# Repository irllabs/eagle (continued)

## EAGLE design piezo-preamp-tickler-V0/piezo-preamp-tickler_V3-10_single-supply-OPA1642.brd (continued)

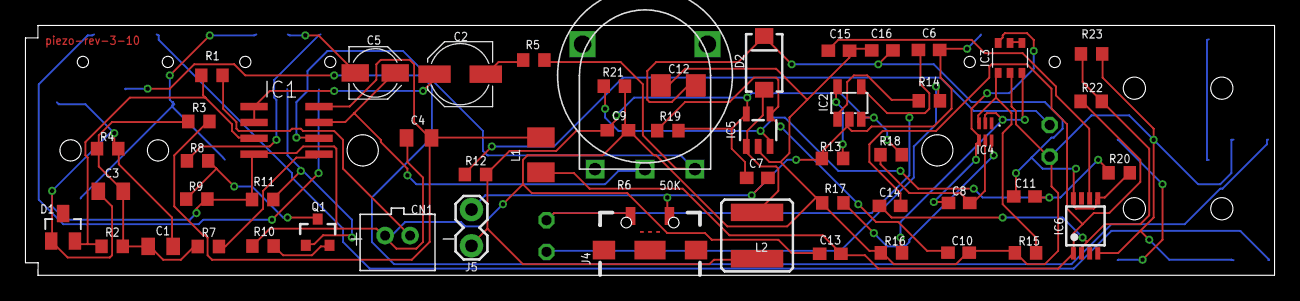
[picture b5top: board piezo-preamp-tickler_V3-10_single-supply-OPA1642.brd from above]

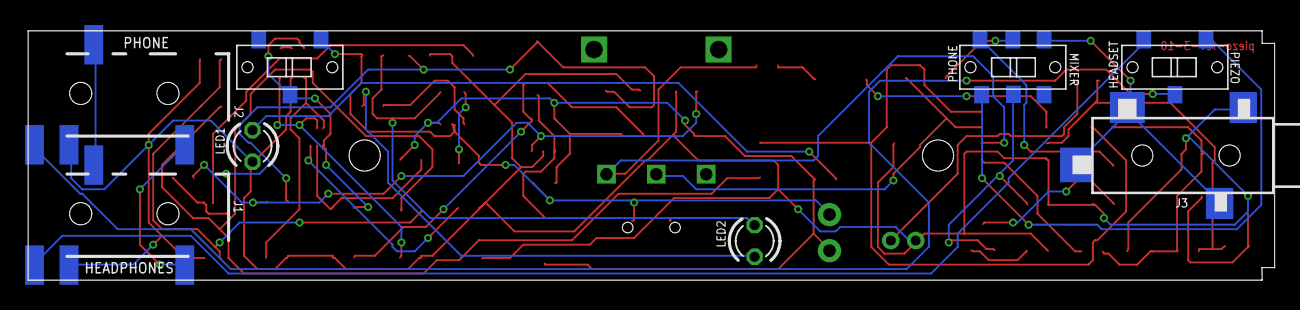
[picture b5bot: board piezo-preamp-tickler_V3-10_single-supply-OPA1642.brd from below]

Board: 2 copper layers, 100.0 x 20.0 mm, 61 parts (8 on the bottom side), 41 nets.

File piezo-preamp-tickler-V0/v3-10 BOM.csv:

"Part";"Value";"Device";"Package";"Description";"PROD_ID";"SPICEPREFIX";
"C1";"10uF";"C-USC0805K";"C0805K";"CAPACITOR, American symbol";"";"";
"C2";"100uF";"CPOL-EUC";"PANASONIC_C";"POLARIZED CAPACITOR, European symbol";"";"";
"C3";"0.1uF";"C-USC0805K";"C0805K";"CAPACITOR, American symbol";"";"";
"C4";"0.1uF";"C-USC0805K";"C0805K";"CAPACITOR, American symbol";"";"";
"C5";"10uF";"CPOL-EUB";"PANASONIC_B";"POLARIZED CAPACITOR, European symbol";"";"";
"C6";"4.7uF";"C-EUC0603";"C0603";"CAPACITOR, European symbol";"";"C";
"C7";"4.7uF";"C-EUC0603";"C0603";"CAPACITOR, European symbol";"";"C";
"C8";"0.1uF";"C-EUC0603";"C0603";"CAPACITOR, European symbol";"";"C";
"C9";"10uF";"C-EUC0603";"C0603";"CAPACITOR, European symbol";"";"C";
"C10";"56nF";"C-EUC0603";"C0603";"CAPACITOR, European symbol";"";"C";
"C11";"2.2pF";"C-EUC0603";"C0603";"CAPACITOR, European symbol";"";"C";
"C12";"68uF";"C-EUC1206";"C1206";"CAPACITOR, European symbol";"";"C";
"C13";"10uF";"C-EUC0603";"C0603";"CAPACITOR, European symbol";"";"C";
"C14";"10nF";"C-EUC0603";"C0603";"CAPACITOR, European symbol";"";"C";
"C15";"10nF";"C-EUC0603";"C0603";"CAPACITOR, European symbol";"";"C";
"C16";"10uF";"C-EUC0603";"C0603";"CAPACITOR, European symbol";"";"C";
"CN1";"";"JST_2PIN-THM";"JST-PH-2-THM";"JST 2-Pin Connectors of various flavors";"";"";
"D1";"BAT54S";"BAT54S";"SOT23";"Schottky Diodes";"";"";
"D2";"B130-13-F";"DIODESMA";"SMA-DIODE";"Diode";"";"";
"IC1";"OPA1642";"OPA1642";"SO08";"";"";"";
"IC2";"MCP73831";"MCP73831";"SOT-23-5";"";"";"";
"IC3";"QS6K1";"QS6K1";"SOT457R_PHILIPS";"";"";"";
"IC4";"BQ297X";"BQ297X-BATTERY-MANAGERLONG";"WSON-6-LONG";"";"";"";
"IC5";"SC4503";"SC4503";"SOT23-5";"";"";"";
"IC6";"TPS7A49";"TPS7A49";"MSOP-8";"";"";"";
"J1";"HEADPHONES";"TRRS-1/8"-3.5MMLGPADS";"TRRS_SJ-43514-SMT-TR";"Audio jack - 3.5mm TRRS variety - two rings.";"";"";
"J2";"PHONE";"TRRS-1/8"-3.5MMLGPADS";"TRRS_SJ-43514-SMT-TR";"Audio jack - 3.5mm TRRS variety - two rings.";"";"";
"J3";"Mixer";"TRS-1/8"-3.5MM";"TRS_SJ-3524-SMT";"";"";"";
"J4";"";"USB_MICRO-BREDUCED_PASTE";"USB-B-MICRO-SMD_RED_PASTE";"USB Type Micro-B Connector";"CONN-11752";"";
"J5";"Battery";"CONN_02LOCK";"1X02_LOCK";"Multi connection point. Often used as Generic Header-pin footprint for 0.1 inch spaced/style header connections";"";"";
"L1";"100uH/±5%/500mA";"L-EUL3225M";"L3225M";"INDUCTOR, European symbol";"";"L";
"L2";"2.7uH";"INDUCTORCR54";"CR54";"Inductors";"";"";
"LED1";"Power";"LED3MM";"LED3MM";"LED";"";"";
"LED2";"Charge";"LED3MM";"LED3MM";"LED";"";"";
"Q1";"MMBFJ201";"J201SOT-23";"SOT23-3";"N-channel JFET";"";"";
"R1";"100K";"R-US_R0603";"R0603";"RESISTOR, American symbol";"";"";
"R2";"10M";"R-US_R0603";"R0603";"RESISTOR, American symbol";"";"";
"R3";"100K";"R-US_R0603";"R0603";"RESISTOR, American symbol";"";"";
"R4";"100K";"R-US_R0603";"R0603";"RESISTOR, American symbol";"";"";
"R5";"2.2K";"R-US_R0603";"R0603";"RESISTOR, American symbol";"";"";
"R6";"50K";"POTTHUMBPOT14";"THUMBPOT14MM";"http://www.taydaelectronics.com/10k-ohm-linear-taper-potenti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";"";"";
"R7";"220";"R-US_R0603";"R0603";"RESISTOR, American symbol";"";"";
"R8";"1K";"R-US_R0603";"R0603";"RESISTOR, American symbol";"";"";
"R9";"1M";"R-US_R0603";"R0603";"RESISTOR, American symbol";"";"";
"R10";"1.2K";"R-US_R0603";"R0603";"RESISTOR, American symbol";"";"";
"R11";"2.2K";"R-US_R0603";"R0603";"RESISTOR, American symbol";"";"";
"R12";"390";"R-US_R0603";"R0603";"RESISTOR, American symbol";"";"";
"R13";"4.7K";"R-US_R0603";"R0603";"RESISTOR, American symbol";"";"";
"R14";"470";"R-US_R0603";"R0603";"RESISTOR, American symbol";"";"";
"R15";"10M";"R-US_R0603";"R0603";"RESISTOR, American symbol";"";"";
"R16";"10M";"R-US_R0603";"R0603";"RESISTOR, American symbol";"";"";
"R17";"2.2k";"R-US_R0603";"R0603";"RESISTOR, American symbol";"";"";
"R18";"330";"R-US_R0603";"R0603";"RESISTOR, American symbol";"";"";
"R19";"15k";"R-US_R0603";"R0603";"RESISTOR, American symbol";"";"";
"R20";"1M";"R-US_R0603";"R0603";"RESISTOR, American symbol";"";"";
"R21";"100k";"R-US_R0603";"R0603";"RESISTOR, American symbol";"";"";
"R22";"100k";"R-US_R0603";"R0603";"RESISTOR, American symbol";"";"";
"R23";"11k";"R-US_R0603";"R0603";"RESISTOR, American symbol";"";"";
"SW1";"SWITCH_DPDT";"SWITCH_DPDT";"SWITCH_DPDT_CL-SB-22B";"";"";"";
"SW2";"INPUT-select";"SWITCH_SPDTCL-SB-12B";"SWITCH_SPDT_CL-SB-12B";"";"";"";
"SW3";"SPDT";"SWITCH_SPDTCL-SB-12B";"SWITCH_SPDT_CL-SB-12B";"";"";"";

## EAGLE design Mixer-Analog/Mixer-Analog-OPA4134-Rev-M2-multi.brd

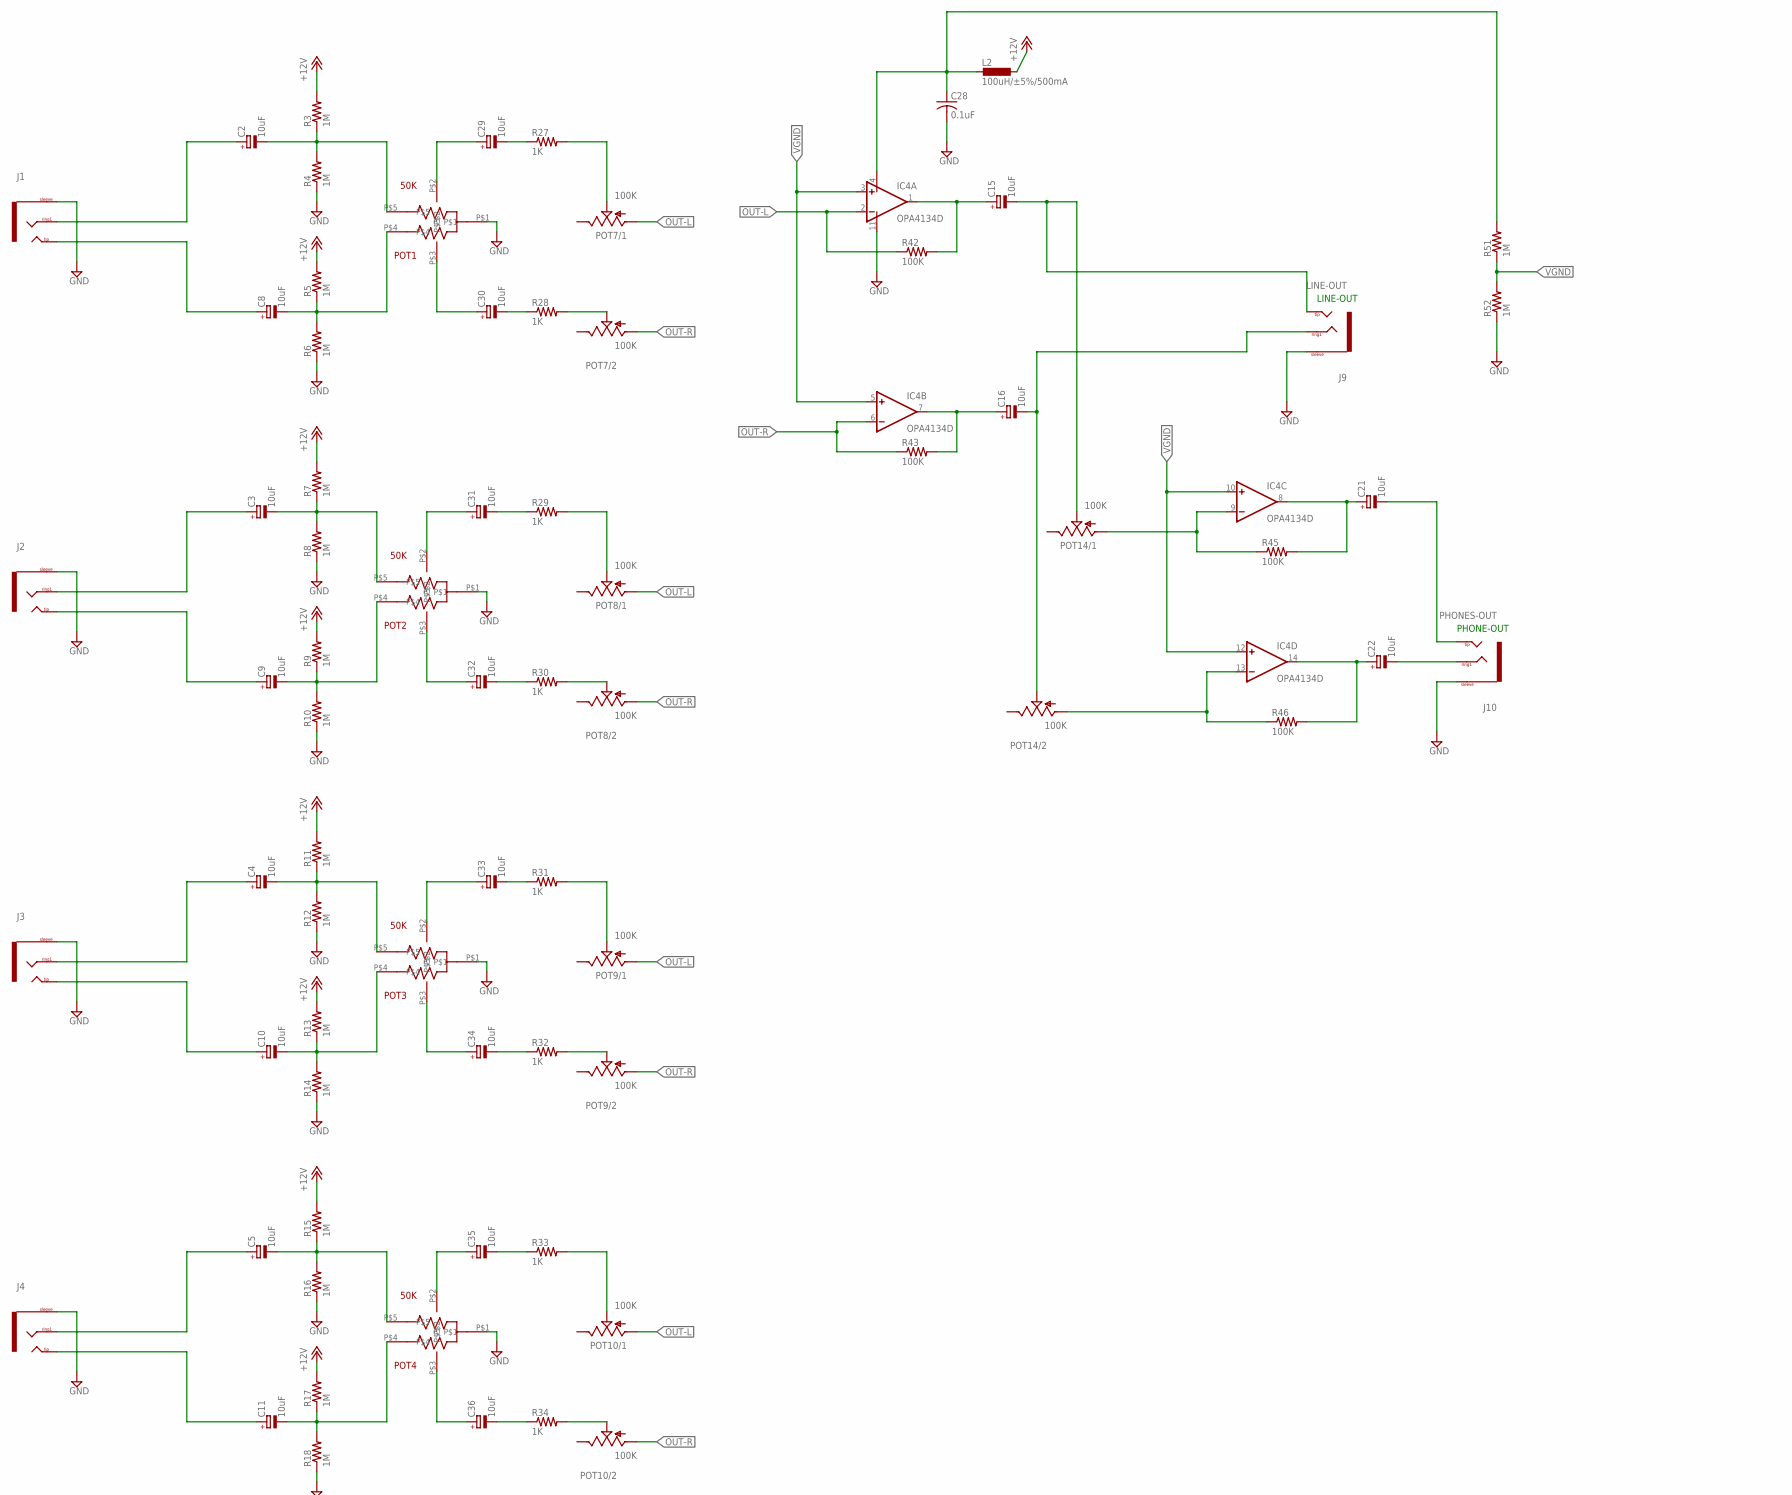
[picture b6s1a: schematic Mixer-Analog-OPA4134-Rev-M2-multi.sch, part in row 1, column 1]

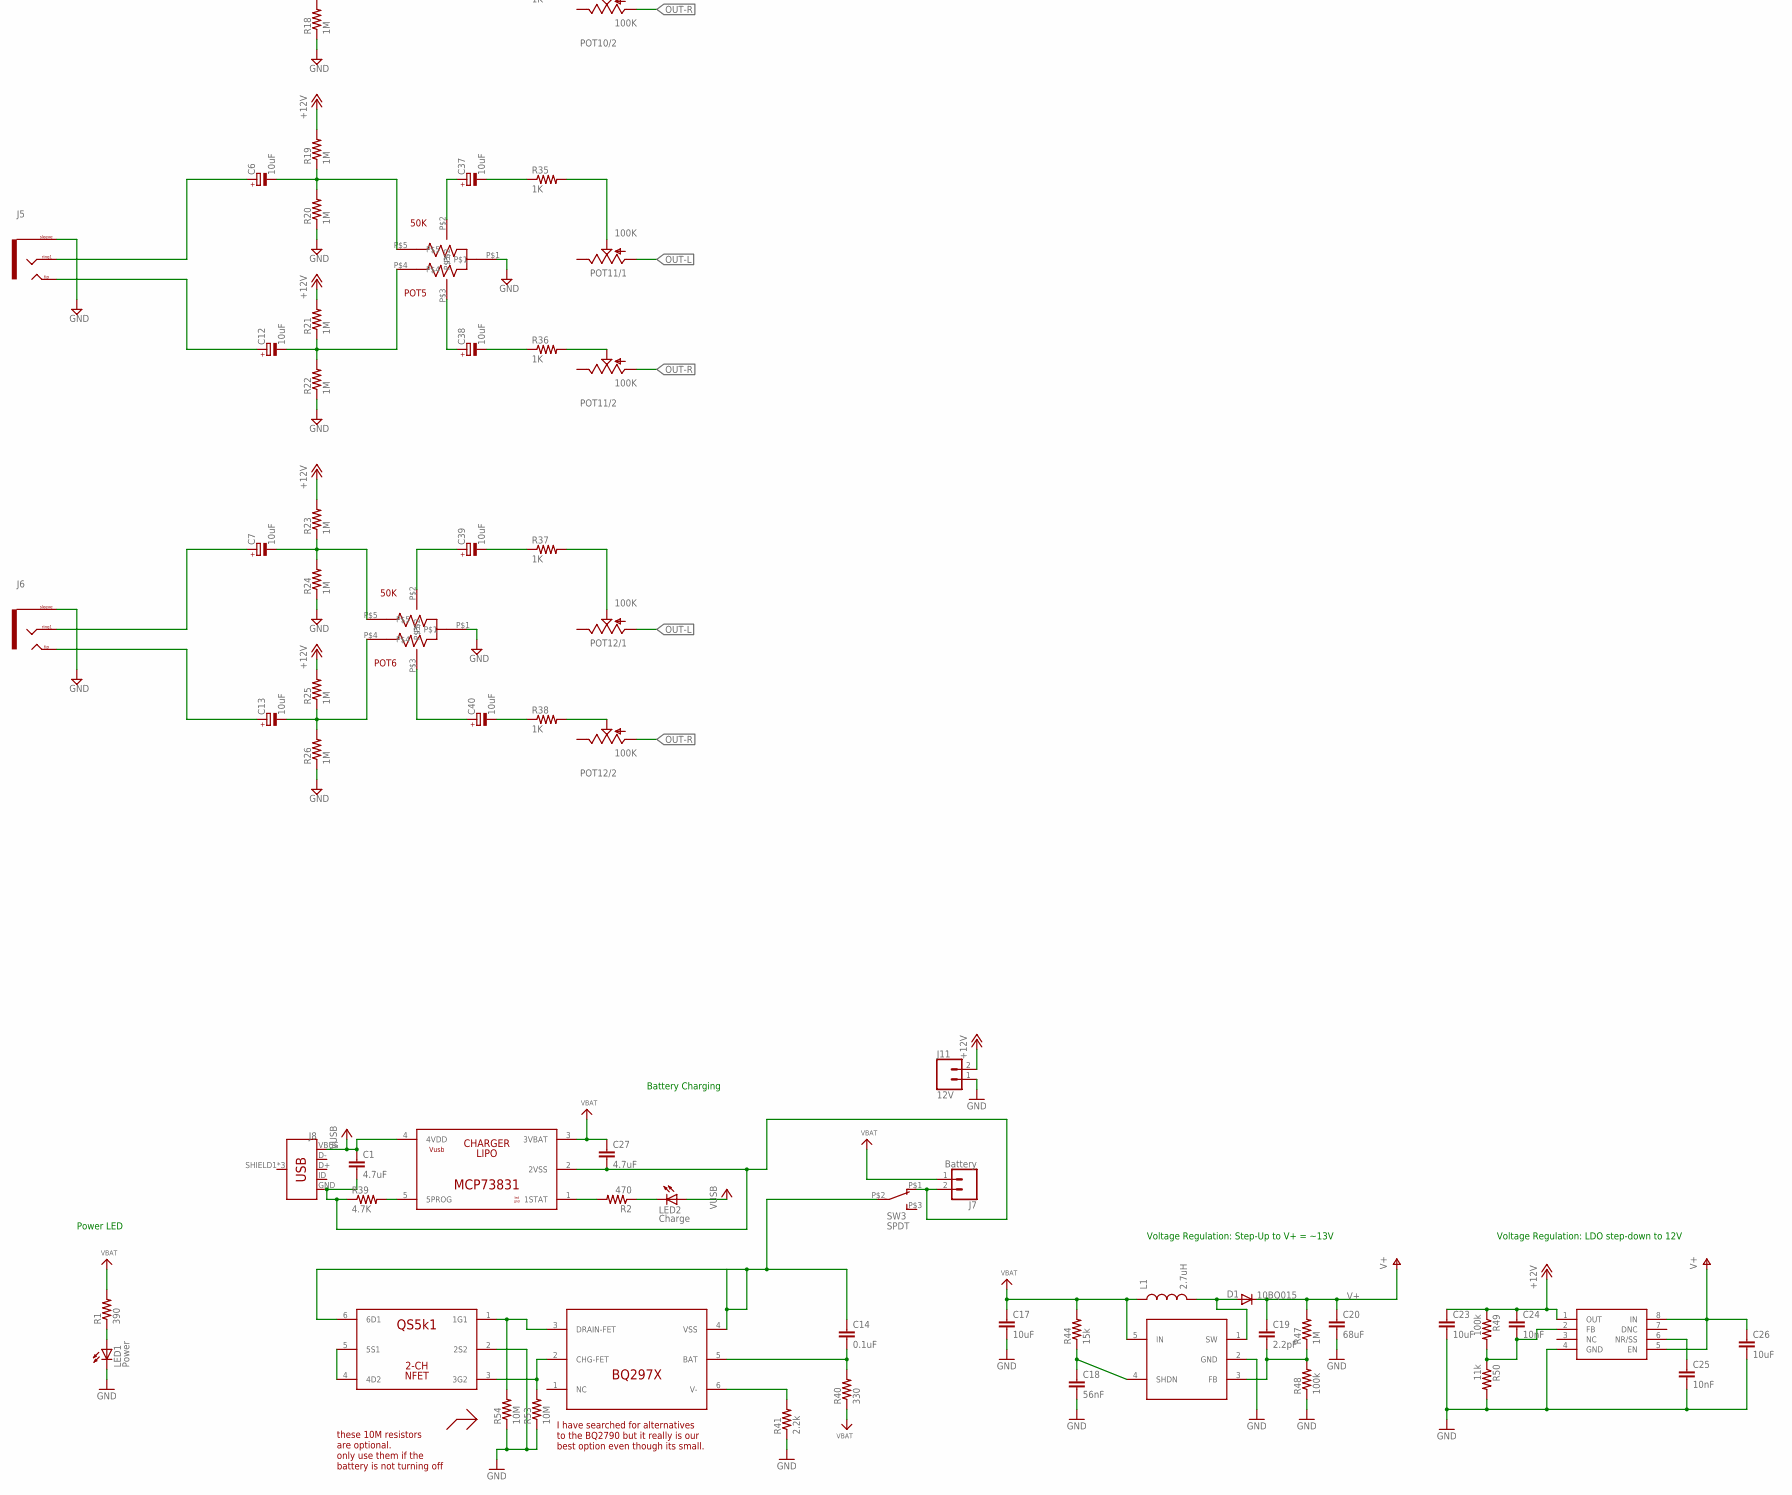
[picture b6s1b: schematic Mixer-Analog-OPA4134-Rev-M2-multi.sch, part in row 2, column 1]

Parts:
C1, C27: 4.7uF; C0603
C2, C3, C4, C5, C6, C7, C8, C9, C10, C11, C12, C13, C15, C16, C21, C22, C29, C30, C31, C32, C33, C34, C35, C36, C37, C38, C39, C40: 10uF; PANASONIC_B
C14: 0.1uF; C0603
C17, C23, C26: 10uF; C0603
C18: 56nF; C0603
C19: 2.2pF; C0603
C20: 68uF; C1206
C24, C25: 10nF; C0603
C28: 0.1uF; C0805K
D1: 10BQ015; SMA-DIODE
IC1: BQ297X; WSON-6-LONG
IC2: MCP73831; SOT-23-5
IC3: QS6K1; SOT457R_PHILIPS
IC4: OPA4134D; SO14
IC5: SC4503; SOT23-5
IC6: TPS7A49; MSOP-8
J1, J2, J3, J4, J5, J6: TRS-1/8"-3.5MM; TRS_SJ-3524-SMT
J7: Battery; 1X02_LOCK
J8: USB_MICRO-BREDUCED_PASTE; USB-B-MICRO-SMD_RED_PASTE
J9: LINE-OUT; TRS_SJ-3524-SMT
J10: PHONES-OUT; TRS_SJ-3524-SMT
J11: 12V; 1X02_LOCK
L1: 2.7uH; CR54-KIT
L2: 100uH/±5%/500mA; L3225M
LED1: Power; LED3MM
LED2: Charge; LED3MM
POT1, POT2, POT3, POT4, POT5, POT6: 50K; POT-DUAL-ALPS-RK10J12E0A0A
POT7, POT8, POT9, POT10, POT11, POT12, POT14: 100K; PTV112
R1: 390; R0603
R2: 470; R0603
R3, R4, R5, R6, R7, R8, R9, R10, R11, R12, R13, R14, R15, R16, R17, R18, R19, R20, R21, R22, R23, R24, R25, R26, R51, R52: 1M; 0603-RES
R27, R28, R29, R30, R31, R32, R33, R34, R35, R36, R37, R38: 1K; 0603-RES
R39: 4.7K; R0603
R40: 330; R0603
R41: 2.2k; R0603
R42, R43, R45, R46: 100K; 0603-RES
R44: 15k; R0603
R47: 1M; R0603
R48, R49: 100k; R0603
R50: 11k; R0603
R53, R54: 10M; R0603
SW3: SPDT; SWITCH_SPDT_CL-SB-12B

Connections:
+5V: C1.1, IC2.4 (4VDD), J8.VBUS, LED2.A
+12V: C23.1, C24.1, IC6.1 (OUT), J11.2, L2.1, R3.2, R5.2, R7.2, R9.2, R11.2, R13.2, R15.2, R17.2, R19.2, R21.2, R23.2, R25.2, R49.1
BATGND: C14.1, IC1.4 (VSS), IC3.6 (6D1), SW3.P$2 (2)
GND: C17.2, C18.2, C20.2, C23.2, C25.2, C26.2, C28.2, IC3.2 (2S2), IC4.11 (V-), IC6.4 (GND), J1.1 (SLEEVE), J2.1 (SLEEVE), J3.1 (SLEEVE), J4.1 (SLEEVE), J5.1 (SLEEVE), J6.1 (SLEEVE), J9.1 (SLEEVE), J10.1 (SLEEVE), J11.1, LED1.K (C), POT1.P$1, POT2.P$1, POT3.P$1, POT4.P$1, POT5.P$1, POT6.P$1, R4.1, R6.1, R8.1, R10.1, R12.1, R14.1, R16.1, R18.1, R20.1, R22.1, R24.1, R26.1, R41.1, R48.1, R50.2, R52.1, R53.1, R54.1
unnamed: C8.+, J1.2 (TIP), J1.4 (TIP)
unnamed: LED2.K (C), R2.1
unnamed: C8.-, POT1.P$4, R5.1, R6.2
unnamed: C14.2, IC1.5 (BAT), R40.2
unnamed: C29.+, POT1.P$2
unnamed: IC2.5 (5PROG), R39.2
unnamed: C15.+, IC4.1 (OUT), R42.2
unnamed: C2.+, J1.3 (RING1)
unnamed: C30.+, POT1.P$3
unnamed: IC2.1 (1STAT), R2.2
unnamed: IC3.4 (4D2), IC3.5 (5S1)
unnamed: IC1.3 (DRAIN-FET), IC3.1 (1G1), R54.2
unnamed: C2.-, POT1.P$5, R3.1, R4.2
unnamed: IC1.2 (CHG-FET), IC3.3 (3G2), R53.2
unnamed: IC4.13 (-IN), POT14.2.1 (A), R46.1
unnamed: C16.+, IC4.7 (OUT), R43.2
unnamed: POT7.2.2 (S), R28.2
unnamed: C30.-, R28.1
unnamed: C22.-, J10.3 (RING1)
unnamed: C9.-, POT2.P$4, R9.1, R10.2
unnamed: C21.-, J10.2 (TIP), J10.4 (TIP)
unnamed: C21.+, IC4.8 (OUT), R45.2
unnamed: C22.+, IC4.14 (OUT), R46.2
unnamed: C31.+, POT2.P$2
unnamed: POT8.1.2 (S), R29.2
unnamed: C9.+, J2.2 (TIP), J2.4 (TIP)
unnamed: C3.+, J2.3 (RING1)
unnamed: C31.-, R29.1
unnamed: C3.-, POT2.P$5, R7.1, R8.2
unnamed: POT8.2.2 (S), R30.2
unnamed: C28.1, IC4.4 (V+), L2.2, R51.2
unnamed: IC1.6 (V-), R41.2
unnamed: C29.-, R27.1
unnamed: C32.-, R30.1
unnamed: C32.+, POT2.P$3
unnamed: C33.+, POT3.P$2
unnamed: C33.-, R31.1
unnamed: C34.-, R32.1
unnamed: C10.-, POT3.P$4, R13.1, R14.2
unnamed: C34.+, POT3.P$3
unnamed: POT9.1.2 (S), R31.2
unnamed: C10.+, J3.2 (TIP), J3.4 (TIP)
unnamed: C4.+, J3.3 (RING1)
unnamed: C35.+, POT4.P$2
unnamed: C4.-, POT3.P$5, R11.1, R12.2
unnamed: POT9.2.2 (S), R32.2
unnamed: C36.+, POT4.P$3
unnamed: C35.-, R33.1
unnamed: C36.-, R34.1
unnamed: C37.+, POT5.P$2
unnamed: C37.-, R35.1
unnamed: C38.+, POT5.P$3
unnamed: POT7.1.2 (S), R27.2
unnamed: C38.-, R36.1
unnamed: C39.+, POT6.P$2
unnamed: C11.-, POT4.P$4, R17.1, R18.2
unnamed: C39.-, R37.1
unnamed: POT10.1.2 (S), R33.2
unnamed: C15.-, J9.2 (TIP), J9.4 (TIP), POT14.1.2 (S)
unnamed: C11.+, J4.2 (TIP), J4.4 (TIP)
unnamed: C5.+, J4.3 (RING1)
unnamed: C40.-, R38.1
unnamed: C5.-, POT4.P$5, R15.1, R16.2
unnamed: POT10.2.2 (S), R34.2
unnamed: C40.+, POT6.P$3
unnamed: C12.-, POT5.P$4, R21.1, R22.2
unnamed: POT11.1.2 (S), R35.2
unnamed: C12.+, J5.2 (TIP), J5.4 (TIP)
unnamed: C6.+, J5.3 (RING1)
unnamed: C6.-, POT5.P$5, R19.1, R20.2
unnamed: POT11.2.2 (S), R36.2
unnamed: C13.-, POT6.P$4, R25.1, R26.2
unnamed: POT12.1.2 (S), R37.2
unnamed: C13.+, J6.2 (TIP), J6.4 (TIP)
unnamed: C7.+, J6.3 (RING1)
unnamed: C7.-, POT6.P$5, R23.1, R24.2
unnamed: POT12.2.2 (S), R38.2
unnamed: LED1.A, R1.1
unnamed: D1.A, IC5.1 (SW), L1.P$2 (2)
unnamed: C18.1, IC5.4 (SHDN), R44.1
unnamed: C19.2, IC5.3 (FB), R47.1, R48.2
unnamed: C24.2, IC6.2 (FB), R49.2, R50.1
unnamed: C25.1, IC6.6 (NR/SS)
OUT-L: IC4.2 (-IN), POT7.1.1 (A), POT8.1.1 (A), POT9.1.1 (A), POT10.1.1 (A), POT11.1.1 (A), POT12.1.1 (A), R42.1
OUT-L1: IC4.9 (-IN), POT14.1.1 (A), R45.1
OUT-R: IC4.6 (-IN), POT7.2.1 (A), POT8.2.1 (A), POT9.2.1 (A), POT10.2.1 (A), POT11.2.1 (A), POT12.2.1 (A), R43.1
OUT-R1: C16.-, J9.3 (RING1), POT14.2.2 (S)
USBGND: C1.2, C27.2, IC2.2 (2VSS), J7.2, J8.GND, R39.1, SW3.P$1 (1)
V+: C19.1, C20.1, C26.1, D1.C, IC6.5 (EN), IC6.8 (IN), R47.2
VBAT: C17.1, C27.1, IC2.3 (3VBAT), IC5.5 (IN), J7.1, L1.P$1 (1), R1.2, R40.1, R44.2
VGND: IC4.3 (+IN), IC4.5 (+IN), IC4.10 (+IN), IC4.12 (+IN), R51.1, R52.2

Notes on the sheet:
LINE-OUT
PHONE-OUT
Voltage Regulation: Step-Up to V+ = ~13V
Power LED
Voltage Regulation: LDO step-down to 12V
Battery Charging
I have searched for alternatives to the BQ2790 but it really is our best option even though its small.
these 10M resistors are optional. only use them if the battery is not turning off

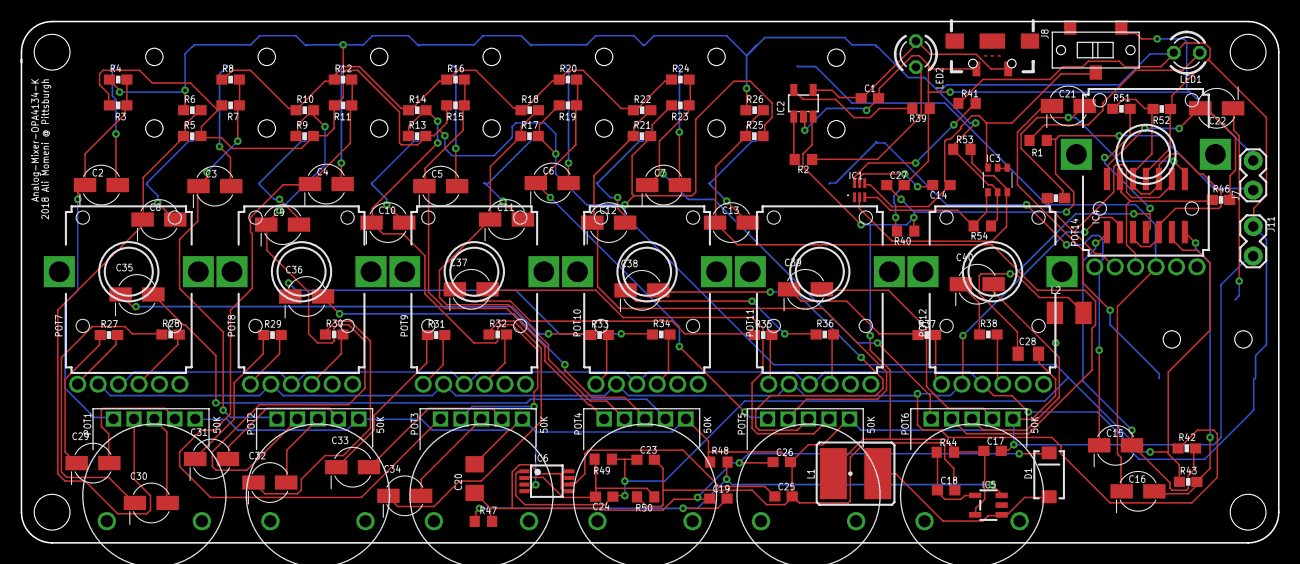
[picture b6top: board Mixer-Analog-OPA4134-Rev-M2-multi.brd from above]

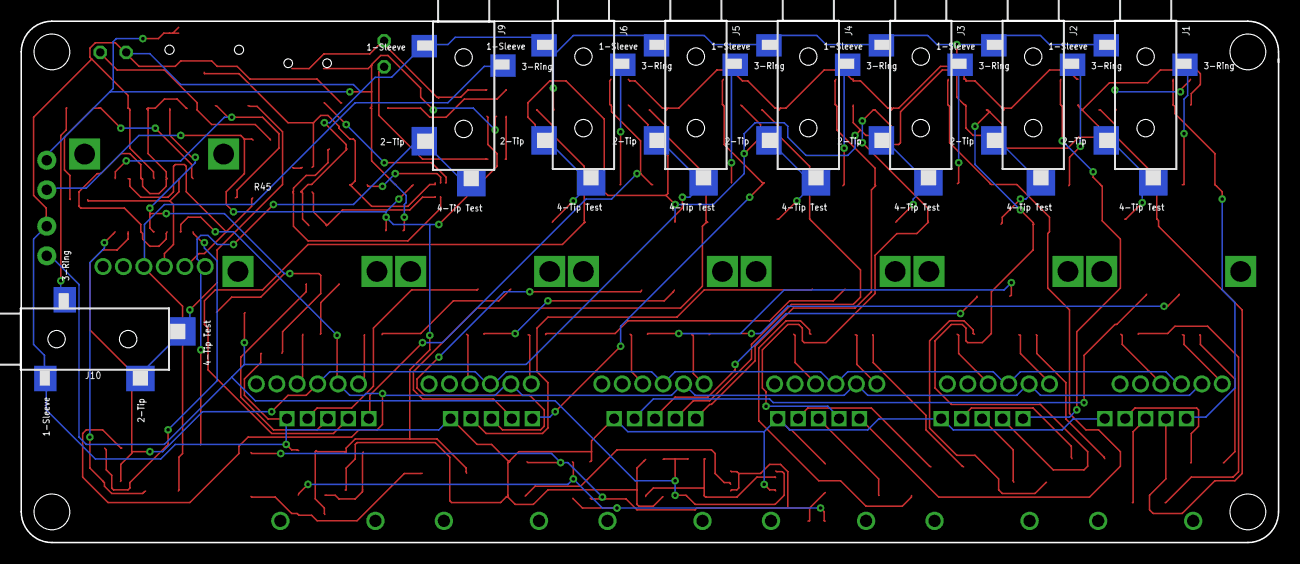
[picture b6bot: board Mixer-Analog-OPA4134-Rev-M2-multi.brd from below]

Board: 2 copper layers, 123.0 x 51.0 mm, 130 parts (8 on the bottom side), 95 nets.

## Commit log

2016-07-01 initial upload
2016-07-06 new version of ritter board
2016-07-20 version 3 of ritter board
2016-07-20 cleaned up ritter v3, added hole
2016-07-20 minor changes to piezo-buffer-and-preamp-ritter_V04
2016-07-20 added simple jack
2016-07-20 simple buffer with jack cleaned up
2016-07-20 latest jack
2016-07-27 Copperclad Board Preamp and Buffer
2016-07-27 added A23 Battery to library
2016-07-27 cleaned up A23
2016-08-01 Added Cooper Buffer
2016-08-01 cooper buffer etch and drill files
2016-08-01 cooper buffer etch and drill files change
2016-08-02 added output to cooper buffer
2016-08-02 cooper buffer gcode added
2016-08-03 Added TRRS Breakout
2016-08-03 Added TRRS Version 2
2016-08-03 Fixed GCode
2016-08-03 Top.Drill Added
2016-08-03 Added Top Drill
2016-08-03 Added GCode for CooperBufferAmp
2016-08-03 Added Bottom GCode CooperBufferAmp
2016-08-04 CooperAmpBuffer V03 Board and GCode Added
2016-08-04 GCode and Board for CooperAmpBuffer 4
2016-08-05 working board with jacks and battery holder
2016-08-05 drill and etch files for new preamp+buffer
2016-08-05 battery holder scaled
2016-08-05 updated gcode for new board
2016-08-05 edited battery holder for artfab lbr
2016-08-10 gcode files and preamp updated to be smaller
2016-08-10 adjusted milling file
2016-08-22 latest board
2016-08-22 reshaped double-sided board
2016-08-24 names changed
2016-08-24 edits for v7 of tickler preamp
2016-08-29 On/Off Added, mounting holes added, HP Jacks Mirrored
2016-08-30 minor changes to tickler board v0.7
2016-09-23 ticklers
2016-10-11 tickler v8
2016-10-20 changes to piezo-preamp-tickler-V0-5
2016-12-06 new tickler board
2016-12-28 changes to TeensyLC midi
2016-12-31 added Daniel Library
2017-01-15 changes to library and ticklerboards
2017-01-21 new tickler preamps
2017-02-04 new MEMS boards
2017-02-16 new mic preamps added
2017-02-20 new tickler boards, new chipchestra boards
2017-03-06 updates to chipchestra
2017-05-10 many changes to chipchestra
2017-05-18 design files with MEMS preamp board (new version)
2017-05-19 chip/MOM updates
2017-05-19 modify the silkscreen layer on board
2017-05-22 MEMS board reorientation
2017-05-23 add new schematic for PIEZO project with 2 buffers
2017-06-03 pizeo-preamp-tickler_V2-RevC.sch added
2017-06-04 new Gutwise power board
2017-06-06 new TRRS
2017-06-09 piezo rev c
2017-06-09 mems and piezo rev c
2017-06-10 ICS40300-preamp-surfacemount_Rev-C added
2017-06-13 piezo with buffer, mems with dual gain
2017-06-13 piezo fix for version C
2017-06-13 piezo cleanup
2017-06-13 piezo dims
2017-06-13 gerbers
2017-06-13 file rename
2017-06-19 fixed gerbers
2017-06-23 rename chipchestra to MOM
2017-07-14 piezo rev d
2017-07-16 MOL PCB v2-1 and Modules revisions
2017-07-17 changes to cmu artfab library for eagle
2017-07-17 library cleanup
2017-07-17 new parts in cmu-artfab.lbr
2017-07-28 Mems Board Updates
2017-07-28 Mems Board Corrections
2017-08-02 Piezo Rev E
2017-08-13 added filter, fixed footprints, sorry
2017-08-14 added gerbers for revE Mems
2017-08-22 piezo rev F
2017-09-15 new library members
2017-09-15 new libr
2017-10-04 just catching the piezo board design
2017-10-06 made a broken out version of the latest board
2017-10-06 updated footprints
2017-10-06 changes to piezo-preamp-tickler_V2-RevG-Breakout -made all names/labels consistent in size/font and readable -moved all parts to top -rearranged (position and rotation) all components to mostly match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
2017-10-06 renumbered parts in piezo-preamp-tickler_V2-RevG-Breakout
2017-10-07 new LM3900 based analog 6-channel audio mixer
2017-10-07 analog mixer reorg
2017-10-08 piezo-preamp-tickler_V2-RevG-Breakout routed and GERBER-ed
2017-11-07 test boards for v3 piezo preamps
2017-12-07 new version so of piezo pickups
2017-12-09 test OPA analog mixers versions C-F
2017-12-12 small updates to analog mixer boards
2017-12-17 new mems preamp added
2017-12-17 new design for piezo premamp piezo-preamp-tickler_V3-2_single-supply-OPA1642 added
2017-12-22 new piezo preamp designs
2017-12-22 new piezo preamp circuit v3-3 added
2017-12-22 My message
2017-12-22 piezo preamp fixes
2017-12-23 piezo preamp updates
2017-12-24 in progress, do not use
2017-12-27 ready for bom picking, just finalizing placement
2017-12-28 should be pretty much good, just not sure what to do about labels
2018-01-05 piezo power fixed
2018-01-05 mems power fixed
2018-01-05 labeled boards added, all silkscreen labels are visable
2018-01-05 updates to piezo preamp
2018-01-05 changed all font size to be consistant
2018-01-06 hopefully finalized piezo preamp piezo-preamp-tickler_V3-4_single-supply-OPA1642
2018-01-06 updates to MEMS preamp /Users/ali/Documents/Development/eagle/MEMS-preamp/MEMS-preamp_v06_Labels.sch
2018-01-07 renamed preamps MEMS-preamp_v07.sch abd piezo-preamp-tickler_V3-5_single-supply-OPA1642
2018-01-07 boards layed out
2018-01-07 piezo and mems preamps updates
2018-01-09 pizeo and mems
2018-02-03 upates
2018-02-07 Add files via upload
    V3-6 added for piezo board
2018-02-09 Add files via upload
    DRC issues fixed for previous changes
2018-02-13 issues 14 and 17 resolved
2018-02-13 Custom device added for 50K pot
2018-02-13 custom device (50K pot) added for piezo board V3_6
2018-02-13 issue #18 solved
2018-02-13 Issues 17 and 19 fixed
2018-02-13 Bug in issue #23 fixed
2018-02-16 Updated mems board for issues #11,13,15,19,21,22
2018-02-16 PTV112 package updated according to datasheet spec
2018-02-17 cam job added
2018-02-18 Vin of ICS40300 changed back to 12V pin for now
2018-02-23 changed charging ic and dual fets
2018-02-24 Issue #24 fixed and additional components added
    The audio jack connection issue was fixed and the additional resistors were added to the board
2018-02-24 updated charging and footprints
2018-02-24 latest footprint changes done
    board updated and CAM files added for fabrication
2018-02-25 PCB Routing Cleaned Up
2018-03-13 Add files via upload
    Changes done to Piezo board V3-7
2018-03-13 Add files via upload
    Changes made to MEMS board V08
2018-03-17 Add files via upload
    IC names changed according to convention
2018-03-19 small changes to piezo preamp v3-7, renamed for TL072
2018-03-20 moved IC6 in piezo preamp, routed jack signals on back side`
2018-03-20 MEMS preamp with electrolytic caps
2018-03-24 gerbers for mems and piezo
2018-03-29 gerbers updated for piezo and mems
2018-04-08 piezo preamp changed back to OPA1642
2018-04-08 resolved cosmetic issues in mems and piezo for 5k and 50k resistor values that should be 4.7k and 47K
2018-04-08 mems v10, rebuilt from v8, to have electrolytic caps
2018-04-08 v10 board updated to solve inconsistencies.
    v08 local copy board was taken as reference and all the updates later were added in order to get a consistent board.
2018-04-08 capacitors renumbered in sequence
2018-04-08 OPA1642 device added from CMU artfab library
2018-04-08 Capacitors changed according to V08
2018-04-16 Version M added
    updates done in version M since version L has issues with annotation between schematic and board.
2018-04-21 MEMS brd updated for C13, C15 and C16 layer issues
2018-04-21 CPOL-EU device added with correct layers
2018-04-21 C16 moved away from SC4503
2018-04-22 Power circuitry updated for issue #43
2018-04-22 Multiple updates
    Rev-M updated for change of capacitors from tantalum to electrolytic.
    Rev-M2 created based on the new schematic provided.
2018-04-23 pot reference changed in both boards
    The pot side hole size update was not reflected in the boards. now they are referenced to the latest version of the device.
2018-04-24 drill sizes updated to 0.3mm (12mil)
2018-06-12 MEMs v11
2018-06-13 MEMs seperate V1
2018-06-13 resized board
2018-06-13 fixes
2018-06-13 drc pass
2018-06-14 center pot
2018-06-14 piezo LED moves
2018-06-14 new Gerber
2018-06-14 MEMS update
2018-06-14 MEMS gerb
2018-06-15 5 pin SMD part added, v13 MEMS begins
2018-06-16 rev14
2018-06-16 rev14 fix
2018-06-16 bigger traces, less vias
2018-06-17 rev14 gerber
2020-01-17 removed V0 from the piezo-premp-tickler folder name becaues it containns all verstions
